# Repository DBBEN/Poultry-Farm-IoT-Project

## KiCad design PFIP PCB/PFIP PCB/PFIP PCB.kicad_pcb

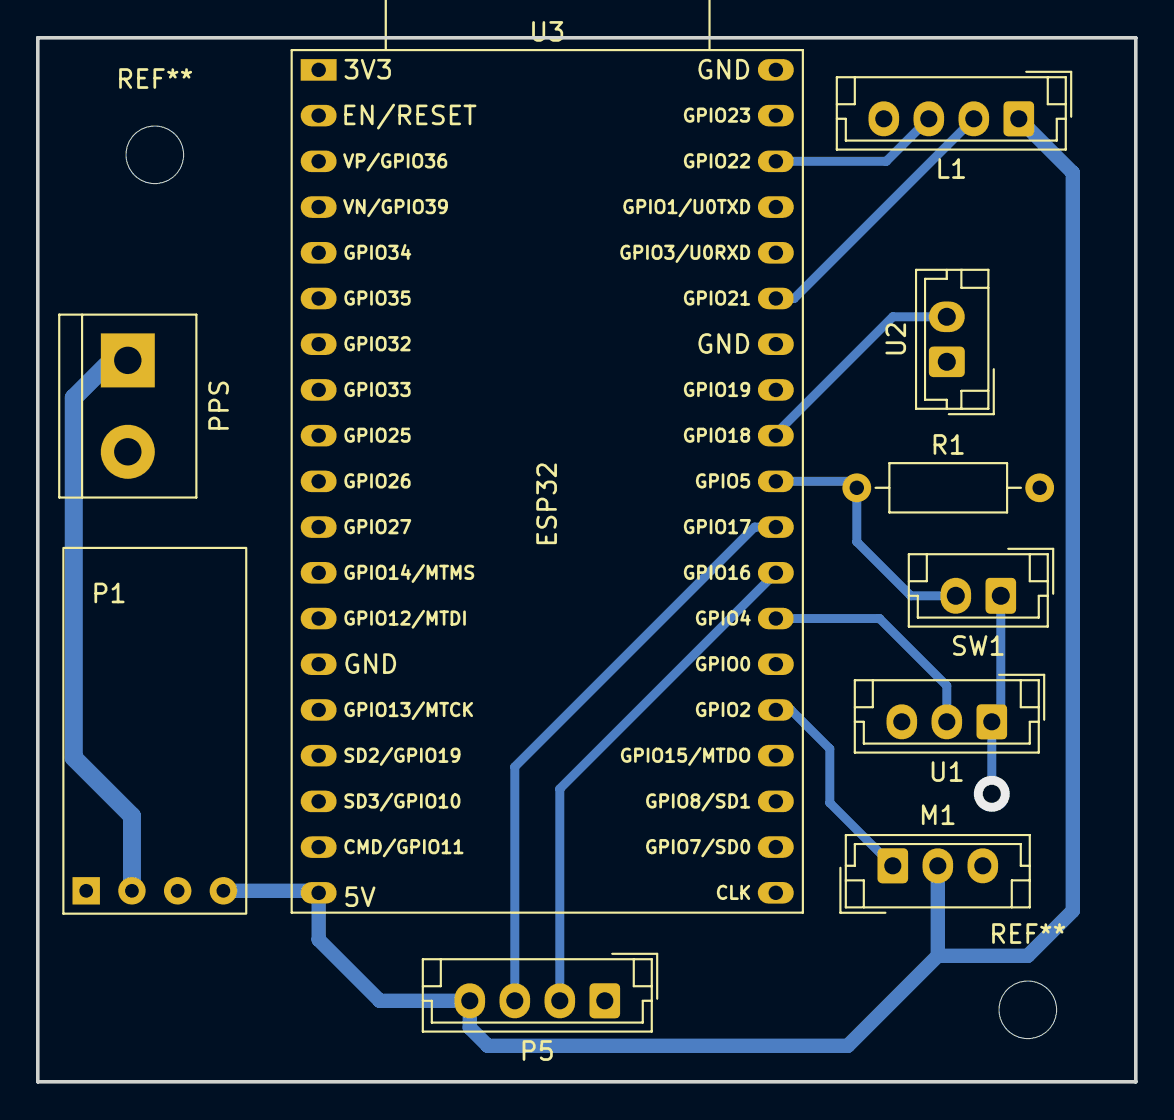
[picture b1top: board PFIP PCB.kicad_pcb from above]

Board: 2 copper layers, 61.0 x 58.0 mm, 10 parts (0 on the bottom side), 12 nets.

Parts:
L1: LCD DISPLAY; JST_EH_B4B-EH-A_1x04_P2.50mm_Vertical
M1: Motor_Servo; JST_EH_B3B-EH-A_1x03_P2.50mm_Vertical
P1: STEP DOWN; Mini Step-Down
P5: PZEM-004T; JST_EH_B4B-EH-A_1x04_P2.50mm_Vertical
PPS: PSU; TerminalBlock_bornier-2_P5.08mm
R1: 10K; R_Axial_DIN0207_L6.3mm_D2.5mm_P10.16mm_Horizontal
SW1: SW_Push; JST_EH_B2B-EH-A_1x02_P2.50mm_Vertical
U1: DHT22 Module; JST_EH_B3B-EH-A_1x03_P2.50mm_Vertical
U2: SSR-D3805HK; JST_EH_B2B-EH-A_1x02_P2.50mm_Vertical
U3: ESP32; ESP32-Module-38pin

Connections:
+3.3V: SW1.1, U1.1 (VCC), U3.1 (3.3V)
+5V: L1.1 (VCC), M1.2 (+), P1.4 (VO+), P5.4 (5V), U3.19 (VIN)
BTN_PIN: R1.1, SW1.2, U3.29 (IO5)
DHT22_OUT: U1.2 (IO), U3.32 (IO4)
GND: L1.4 (GND), M1.3 (-), P1.3 (GND), P5.1 (GND), PPS.2 (12VDC_-), R1.2, U1.3 (GND), U2.1, U3.14 (GND), U3.20 (GND), U3.26 (GND)
I2C_SCL: L1.3 (SCL), U3.22 (IO22)
I2C_SDA: L1.2 (SDA), U3.25 (IO21)
unnamed: P1.2 (IN+), PPS.1 (12VDC_+)
SERVO: M1.1 (PWM), U3.34 (IO2)
SSRELAY_PIN: U2.2, U3.28 (IO18)
UART_RX: P5.3 (RX), U3.30 (IO17)
UART_TX: P5.2 (TX), U3.31 (IO16)

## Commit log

2023-11-07 Firebase Account Changed
2023-11-08 Solved disconnecting issues
2023-11-09 Corrections
2023-11-10 Created bottom navigation
2023-11-11 Added power switch button UI
2023-11-11 Power switch function on device from app
2023-11-13 Added Graph and kWH Pricing
2023-11-14 Added Set Feeding Time & Set Voltage
2023-11-14 Build APK
2023-11-14 Added checkAlarm Function
2023-11-14 Activate servo on set time
2023-11-25 Energy value error solved
2024-01-15 Wifi autoconnect
2024-07-13 Icon and App name Change
2024-07-13 Icon Change
2024-07-15 Fatality Rate Feature Added
2024-08-23 Search records & UI Revision
2024-08-26 Revisions Passed
2024-08-27 Case Sensitive Search
2024-08-28 App Graph Gradient Revision
